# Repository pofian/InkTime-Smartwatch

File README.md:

# InkTime - Smartwatch

InkTime is an open-source, ultra-low-power smartwatch built around the Nordic nRF52840 SoC. It features a 1.54" E-Paper display, integrated battery management, and environmental/motion sensors, all optimized for extended battery life and BLE connectivity.

---

## Hardware Architecture

### Block Diagram

---

## Bill of Materials

| Reference Designators                                                                                                      | Quantity | Description                                                                                                               | Package                                    | Value                                                   | Manufacturer | Manufacturer Part Number | Vendor | Vendor Part Number | Top/Bottom |   |
|----------------------------------------------------------------------------------------------------------------------------|----------|---------------------------------------------------------------------------------------------------------------------------|--------------------------------------------|---------------------------------------------------------|--------------|--------------------------|--------|--------------------|------------|---|
|                                                                                                                            | 1        | PCB Board                                                                                                                 | Board                                      |                                                         |              |                          |        |                    |            |   |
| ANT1                                                                                                                       | 1        | Antennas 2.45GHz ANTENNA                                                                                                  | 2450AT18B100E_ANTC3216X140N                | 2450AT18B100E_2450AT18B100E                             |              |                          |        |                    | Top        |   |
| C1, C2, C17, C18                                                                                                           | 4        | Generic chip capacitor                                                                                                    | NORDIC_NRF_3_RESC0201_L                    | 12pF                                                    |              |                          |        |                    | Top        |   |
| C1-EP-DR, C24, C39                                                                                                         | 3        | CAPACITOR, European symbol                                                                                                | ESP32_WROVER_EAGLE-LTSPICE_C0402           | 10uF                                                    |              |                          |        |                    | Top        |   |
| C2-EP-DR                                                                                                                   | 1        | CAPACITOR, European symbol                                                                                                | ESP32_WROVER_EAGLE-LTSPICE_C0402           | 4.7uF/25V                                               |              |                          |        |                    | Top        |   |
| C3, C4                                                                                                                     | 2        | Generic chip capacitor                                                                                                    | NORDIC_NRF_3_RESC0201_L                    | 1pF                                                     |              |                          |        |                    | Top        |   |
| C5, C7, C8, C12, C19                                                                                                       | 5        | Generic chip capacitor                                                                                                    | NORDIC_NRF_3_RESC0201_L                    | 100nF                                                   |              |                          |        |                    | Top        |   |
| C6, C14, C20, C21                                                                                                          | 4        | Generic chip capacitor                                                                                                    | NORDIC_NRF_3_RESC0201_L                    | 4.7μF                                                   |              |                          |        |                    | Top        |   |
| C9                                                                                                                         | 1        | Generic chip capacitor                                                                                                    | NORDIC_NRF_3_RESC0201_L                    | 820pF                                                   |              |                          |        |                    | Top        |   |
| C10, C13, C22                                                                                                              | 3        | Generic chip capacitor                                                                                                    | NORDIC_NRF_3_RESC0201_L                    | N.C.                                                    |              |                          |        |                    | Top        |   |
| C11                                                                                                                        | 1        | Generic chip capacitor                                                                                                    | NORDIC_NRF_3_RESC0201_L                    | 100pF                                                   |              |                          |        |                    | Top        |   |
| C15                                                                                                                        | 1        | Generic chip capacitor                                                                                                    | NORDIC_NRF_3_RESC0201_L                    | 1.0μF                                                   |              |                          |        |                    | Top        |   |
| C16                                                                                                                        | 1        | Generic chip capacitor                                                                                                    | NORDIC_NRF_3_RESC0201_L                    | 47nF                                                    |              |                          |        |                    | Top        |   |
| C23                                                                                                                        | 1        | Check availability                                                                                                        | CAPC0201X13N                               | 0.1uF                                                   |              |                          |        |                    | Top        |   |
| C25, C33                                                                                                                   | 2        | CAPACITOR, European symbol                                                                                                | ESP32_WROVER_EAGLE-LTSPICE_C0402           | 22uF                                                    |              |                          |        |                    | Top        |   |
| C27, C34                                                                                                                   | 2        | Generic chip capacitor                                                                                                    | NORDIC_NRF_3_RESC0201_L                    | 0.1uF                                                   |              |                          |        |                    | Top        |   |
| C29, C30, C31, C43                                                                                                         | 4        | CAPACITOR, European symbol                                                                                                | ESP32_WROVER_EAGLE-LTSPICE_C0402           |                                                         |              |                          |        |                    | Top        |   |
| C32, C37, C38                                                                                                              | 3        | CAPACITOR, European symbol                                                                                                | ESP32_WROVER_EAGLE-LTSPICE_C0402           | 1uF                                                     |              |                          |        |                    | Top        |   |
| C42                                                                                                                        | 1        | Generic chip capacitor                                                                                                    | NORDIC_NRF_3_RESC0201_L                    |                                                         |              |                          |        |                    | Top        |   |
| D2, D4, D5                                                                                                                 | 3        | ON SEMICONDUCTOR - MBR0530 - DIODE, SCHOTTKY, 0.5A, 30V, SOD-123                                                          | SOD3716X135N                               | ESP32_C6_LIBRARY_5_MBR0530                              |              |                          |        |                    | Top        |   |
| D3                                                                                                                         | 1        | Low Cap. ESD Protection Auto SOT-23-6 STMicroelectronics USBLC6-2SC6Y, Dual Uni-Directional TVS Diode Array, 6-Pin SOT-23 | SOT95P280X145-6N                           | ESP32_C6_LIBRARY_3_USBLC6-2SC6Y                         |              |                          |        |                    | Top        |   |
| EPD_C1, EPD_C2, EPD_C6, EPD_C7, EPD_C8, EPD_C9, EPD_C10, EPD_C11, EPD_C12                                                  | 9        | CAPACITOR, European symbol                                                                                                | ESP32_WROVER_EAGLE-LTSPICE_C0402           | 1uF/50V                                                 |              |                          |        |                    | Top        |   |
| EPD_C5                                                                                                                     | 1        | CAPACITOR, European symbol                                                                                                | ESP32_WROVER_EAGLE-LTSPICE_C0402           | 0.1uF/50V                                               |              |                          |        |                    | Top        |   |
| IC1                                                                                                                        | 1        | Charger IC Lithium Ion/Polymer, Lithium Iron Phosphate 8-DSBGA (1.6x1.1)                                                  | BQ25180YBGR_BGA8C40P2X4_100X155X50         | BQ25180YBGR_BQ25180YBGR                                 |              |                          |        |                    | Top        |   |
| IC2                                                                                                                        | 1        | Haptic Driver for ERM/LRA with Built-In Library and Smart Loop Architecture                                               | DRV2605YZFR_BGA9C50P3X3_144X144X62         | DRV2605YZFR_DRV2605YZFR                                 |              |                          |        |                    | Top        |   |
| IC3                                                                                                                        | 1        | Accelerometers Triaxial low-g 12bit Acceleration Sensor                                                                   | BMA423_BMA423                              | BMA423_BMA423                                           |              |                          |        |                    | Top        |   |
| IC9                                                                                                                        | 1        | Buck-Boost Regulator Positive Output Step-Up/Step-Down I2C DC-DC Controller IC 15-WL-CSP (BSC) (1.4x2.3)                  | RT6160AWSC_BGA15C40P3X5_140X230X60         | RT6160AWSC_RT6160AWSC                                   |              |                          |        |                    | Top        |   |
| J1                                                                                                                         | 1        | FFC & FPC Connectors 0.5mm FPC RA SMT Dual Contact 24Ckt                                                                  | 503480-2400_5034802400                     | 503480-2400_503480-2400                                 |              |                          |        |                    | Top        |   |
| J2                                                                                                                         | 1        | CABLE ADAPTER 6 POS                                                                                                       | TC2030-IDC_TC2030IDC                       | TC2030-IDC_TC2030-IDC                                   |              |                          |        |                    | Top        |   |
| J4                                                                                                                         | 1        | Check availability                                                                                                        | KINGHELM_KH-TYPE-C-16P                     | KH-TYPE-C-16P_KH-TYPE-C-16P                             |              |                          |        |                    | Top        |   |
| L1, L7                                                                                                                     | 2        | Generic chip inductor                                                                                                     | NORDIC_NRF_2_RESC0402_L                    |                                                         |              |                          |        |                    | Top        |   |
| L2                                                                                                                         | 1        | Generic chip inductor                                                                                                     | NORDIC_NRF_2_RESC0402_L                    | 10uH                                                    |              |                          |        |                    | Top        |   |
| L3                                                                                                                         | 1        | Generic chip inductor                                                                                                     | NORDIC_NRF_2_RESC0402_L                    | 15nH                                                    |              |                          |        |                    | Top        |   |
| L5                                                                                                                         | 1        | Generic chip inductor                                                                                                     | NORDIC_NRF_2_RESC0402_L                    | 68uH                                                    |              |                          |        |                    | Top        |   |
| Q1                                                                                                                         | 1        | P-channel MOSFETs                                                                                                         | ESP32_WROVER_SPARKFUN-DISCRETESEMI_SOT23-3 | 20V/4.2A/52mΩ/1.4W                                      |              |                          |        |                    | Top        |   |
| Q3                                                                                                                         | 1        | MOSFET N-Ch 30V 1.5A TrenchFET SC70 Vishay Si1308EDL-T1-GE3 N-channel MOSFET Transistor, 1.5 A, 30 V, 3-Pin SC-70         | SOT65P210X110-3N                           | ESP32_C6_LIBRARY_6_SI1308EDL-T1-GE3                     |              |                          |        |                    | Top        |   |
| R_PWR_EPD, R2_EP_DR, R5, R7, R8, R9                                                                                        | 6        | 7.68k 0201 Thin Film Surface Mount Fixed Resistor +/-0.5% 0.031W CPF0201D7K68C1                                           | CPF0201D7K68C1_0201                        | 10K                                                     |              |                          |        |                    | Top        |   |
| R_TYPE_SEL                                                                                                                 | 1        | 7.68k 0201 Thin Film Surface Mount Fixed Resistor +/-0.5% 0.031W CPF0201D7K68C1                                           | CPF0201D7K68C1_0201                        | 2.2                                                     |              |                          |        |                    | Top        |   |
| R1_EP_DR                                                                                                                   | 1        | 7.68k 0201 Thin Film Surface Mount Fixed Resistor +/-0.5% 0.031W CPF0201D7K68C1                                           | CPF0201D7K68C1_0201                        | 0.47                                                    |              |                          |        |                    | Top        |   |
| R1_USB, R2_USB                                                                                                             | 2        | 7.68k 0201 Thin Film Surface Mount Fixed Resistor +/-0.5% 0.031W CPF0201D7K68C1                                           | CPF0201D7K68C1_0201                        | 5K1                                                     |              |                          |        |                    | Top        |   |
| R2, R4                                                                                                                     | 2        | 7.68k 0201 Thin Film Surface Mount Fixed Resistor +/-0.5% 0.031W CPF0201D7K68C1                                           | CPF0201D7K68C1_0201                        | 0                                                       |              |                          |        |                    | Top        |   |
| R3                                                                                                                         | 1        | 7.68k 0201 Thin Film Surface Mount Fixed Resistor +/-0.5% 0.031W CPF0201D7K68C1                                           | R0201                                      | 0                                                       |              |                          |        |                    | Top        |   |
| R17, R18                                                                                                                   | 2        | 7.68k 0201 Thin Film Surface Mount Fixed Resistor +/-0.5% 0.031W CPF0201D7K68C1                                           | CPF0201D7K68C1_0201                        | 3K3                                                     |              |                          |        |                    | Top        |   |
| SJ1                                                                                                                        | 1        | SMD solder JUMPER                                                                                                         | JUMPER_SJ                                  |                                                         |              |                          |        |                    | Top        |   |
| SW_DN, SW_ENT, SW_UP                                                                                                       | 3        |                                                                                                                           | SW_EVP-AKE31A_PAN                          | 2025-10-22_07-23-44_LIBRARY_EVP-AKE31ASW_EVP-AKE31A_PAN |              |                          |        |                    | Top        |   |
| TP_3.3V, TP_3V3, TP_BAT_GND, TP_GND, TP_ON, TP_OP, TP_RESET, TP_SCL, TP_SDA, TP_SWDCLK, TP_SWDIO, TP_SWO, TP_VBAT, TP_VREG | 14       | Test pad                                                                                                                  | HECTOR_WATCH_1_TP20R                       | HECTOR_WATCH_1_TPTP20R                                  |              |                          |        |                    | Top        |   |
| U1                                                                                                                         | 1        | nRF52840                                                                                                                  | NORDIC_NRF_4_AQFN50P700X700X85_HS-74N      | NORDIC_NRF_4_NRF52840_QF                                |              |                          |        |                    | Top        |   |
| U3                                                                                                                         | 1        | Check availability                                                                                                        | SON50P200X200X80-9N                        | ESP32_C6_LIBRARY_MAX17048G+T10                          |              |                          |        |                    | Top        |   |
| X1                                                                                                                         | 1        |                                                                                                                           | NORDIC_NRF_BT-XTAL_2016_N                  | 32MHz                                                   |              |                          |        |                    | Top        |   |
| X2                                                                                                                         | 1        |                                                                                                                           | NORDIC_NRF_1_XTAL_3215_N                   |                                                         |              |                          |        |                    | Top        |   |

---

## Hardware Functionality

### 1. Power Architecture
The system is powered by a 250mAh LiPo battery.

* **Charging:** The BQ25180 manages 5V input from USB-C. It features I2C configurable charge currents and safety timers.
* **Regulation:** A high-efficiency RT6160 buck-boost converter provides a stable 3.3V rail. This maintains 3.3V even when the battery drops to 3.0V.
* **Monitoring:** The MAX17048 uses the ModelGauge algorithm to provide precise SOC (State of Charge) data.

### 2. Display System
A 1.54" E-Paper display (200x200) is used for zero power consumption when static.

* **Interface:** 4-wire SPI + DC/RST/BUSY control lines.
* **Booster Circuit:** An external inductor-based boost circuit generates the ±15V gates voltages required for the e-ink capsules.

### 3. Sensors and Feedback
* **IMU:** The BMA423 provides step counting and tilt-to-wake functionality via I2C interrupts.
* **Haptics:** The DRV2605 drives a 10mm coin vibration motor, providing tactile effects.

---

## Design Log & Decisions

### DRC Exceptions
The following errors were reviewed and manually accepted in the final design:

* **Pad-to-Trace Clearance:** Errors caused by traces passing between MCU pads; these are unavoidable due to the high-density pinout and the limited routing escape paths of the nRF52840 package.
* **Via Proximity:** Errors caused by vias placed in close proximity to each other, necessitated by the same spatial constraints in the micro-pitch area of the SoC.

### Layout Decisions
* **Stack-up:** 4-layer PCB to ensure a solid GND plane (Layer 2) for RF performance.
* **Power Traces:** All power rails (VBUS, VBAT, 3V3, etc.) use a 0.3mm width for current spikes.
* **Signal Integrity:** Data signals use 0.15mm width. No 90-degree angles were used; all corners are 45 degrees.

### Mechanical Placement
* **USB-C Port:** Centered on the top edge, slightly protruding from the PCB boundary for seamless enclosure alignment.
* **User Input:** Three tactile buttons are located on the bottom edge.

### Polygon & Outline Management
* **GND Polygon Overlaps:** Same-net (GND) clearance warnings between overlapping polygons on different layers were ignored as they pose no electrical risk.

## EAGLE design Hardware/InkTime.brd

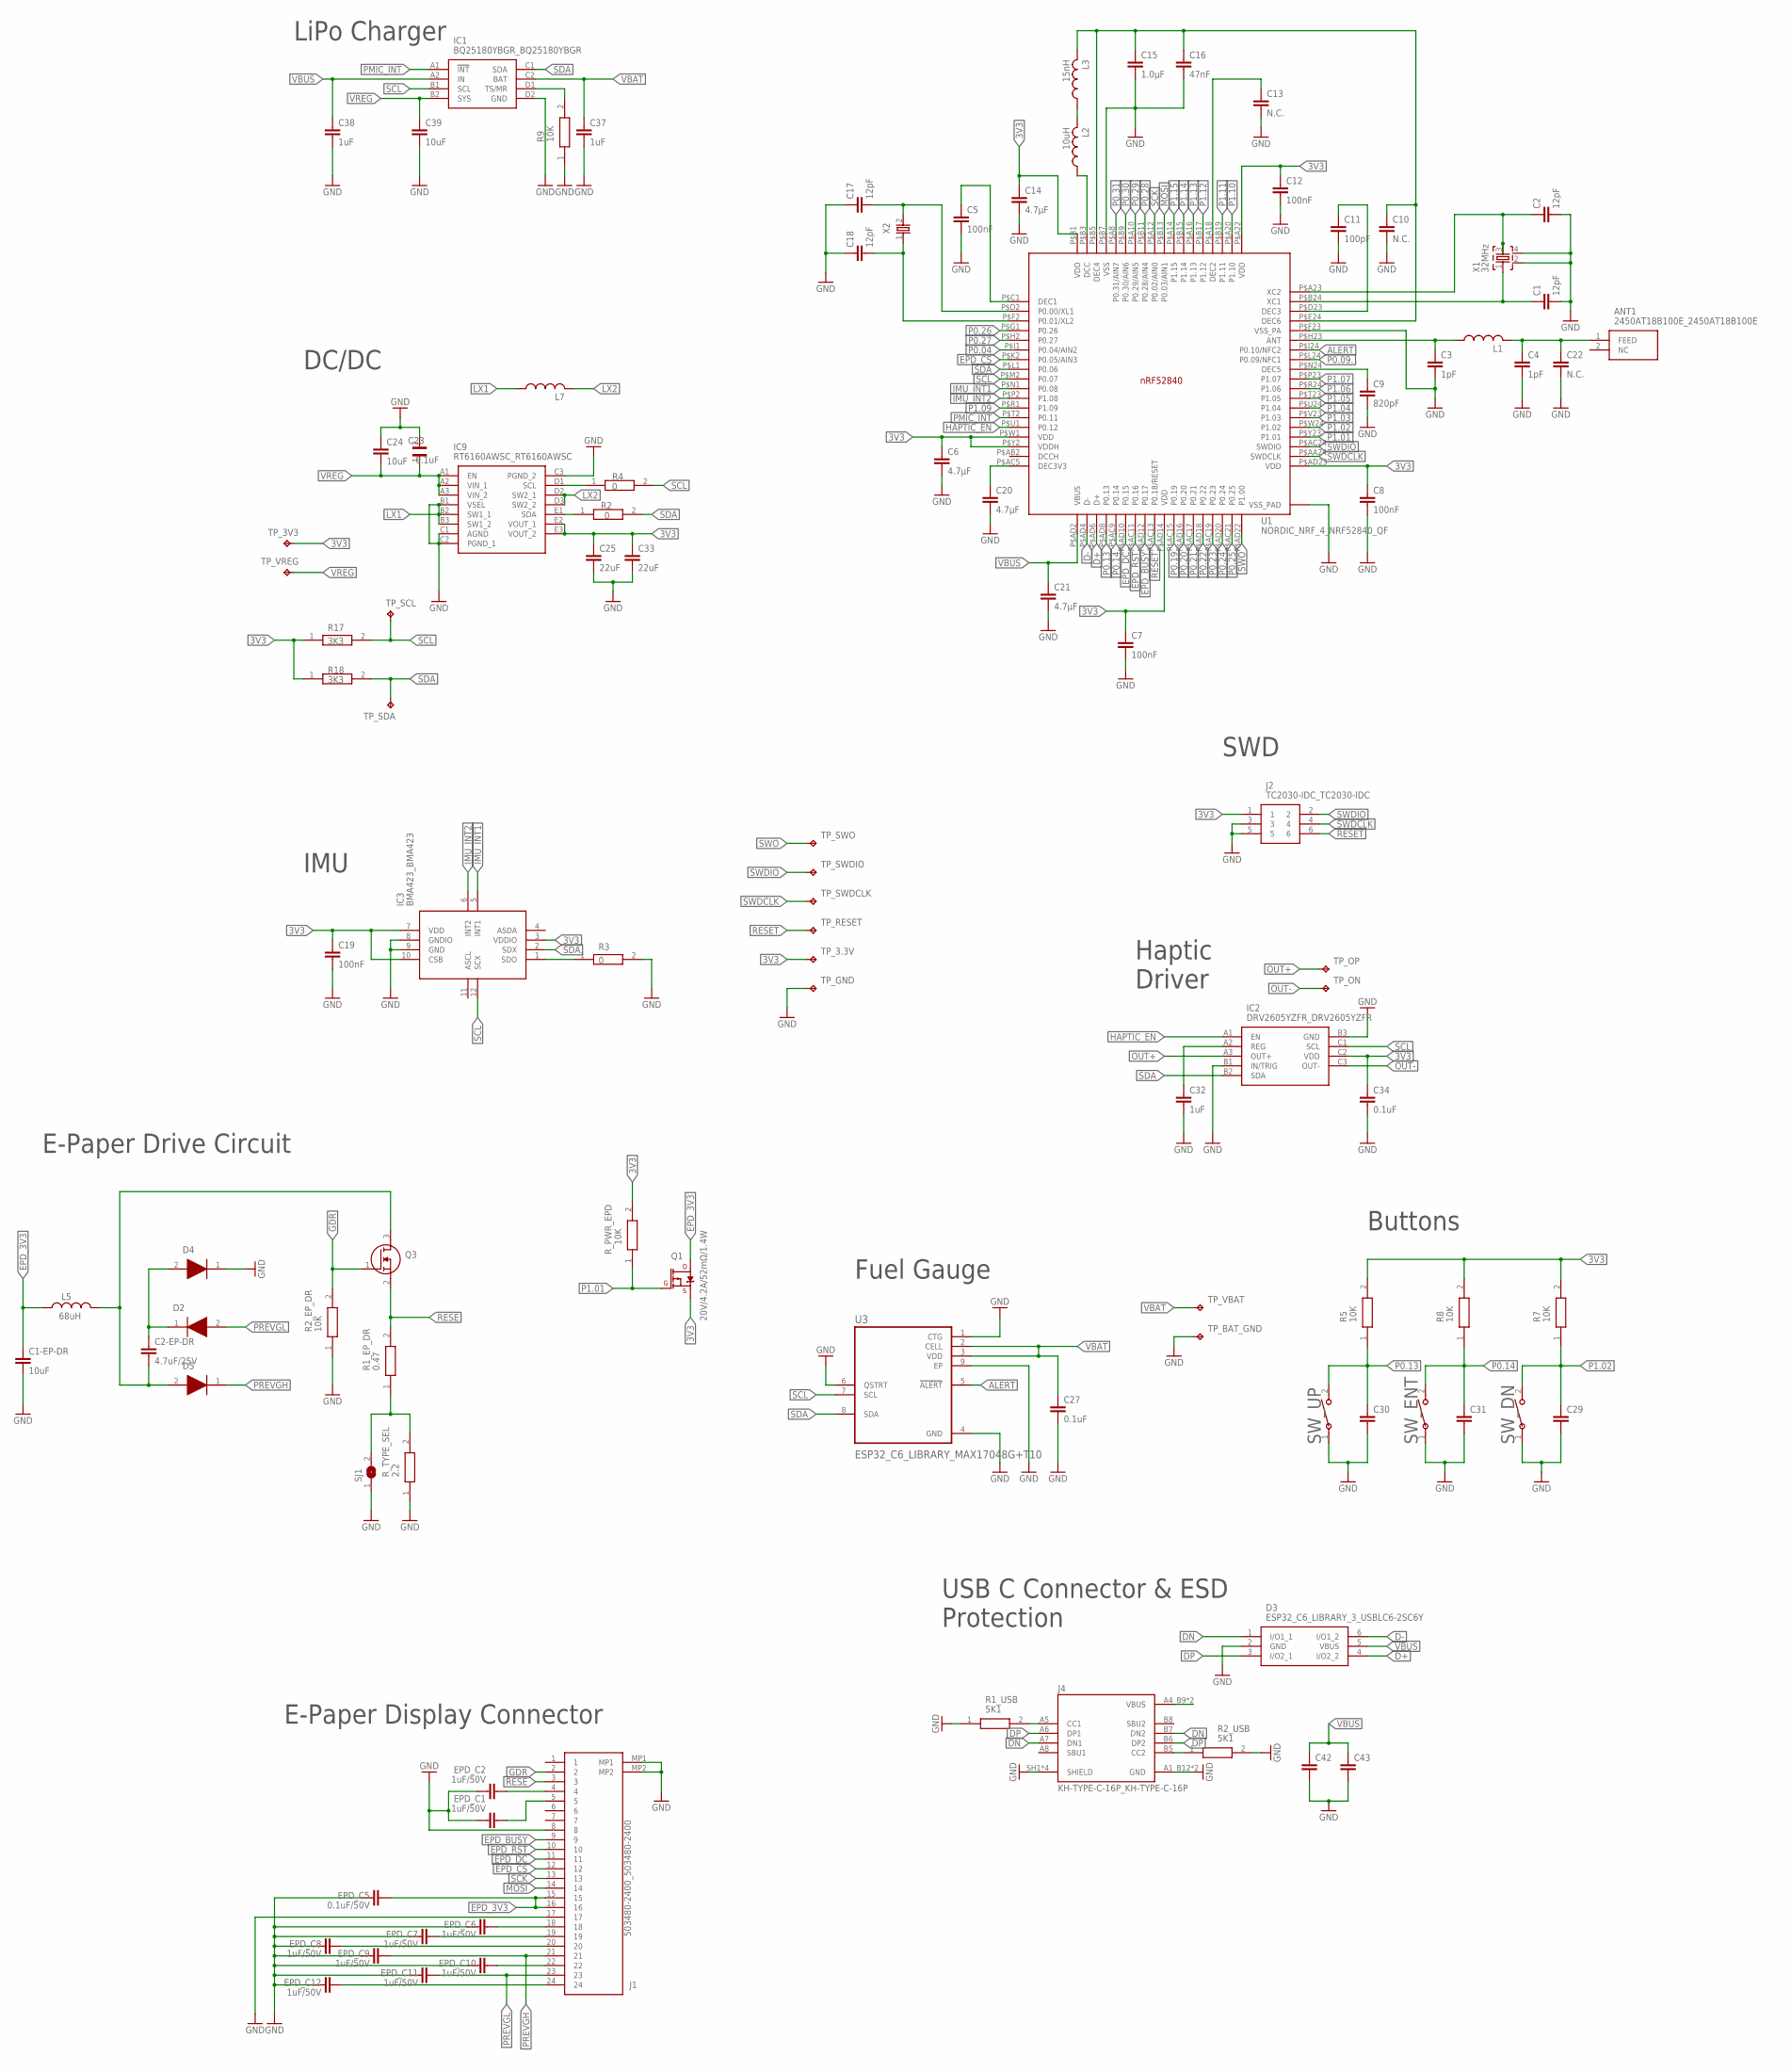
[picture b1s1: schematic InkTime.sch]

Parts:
ANT1: 2450AT18B100E_2450AT18B100E; 2450AT18B100E_ANTC3216X140N
C1, C2, C17, C18: 12pF; NORDIC_NRF_3_RESC0201_L
C1-EP-DR, C24, C39: 10uF; ESP32_C6_LIBRARY_1_ESP32_WROVER_EAGLE-LTSPICE_C0402
C2-EP-DR: 4.7uF/25V; ESP32_C6_LIBRARY_1_ESP32_WROVER_EAGLE-LTSPICE_C0402
C3, C4: 1pF; NORDIC_NRF_3_RESC0201_L
C5, C7, C8, C12, C19: 100nF; NORDIC_NRF_3_RESC0201_L
C6, C14, C20, C21: 4.7μF; NORDIC_NRF_3_RESC0201_L
C9: 820pF; NORDIC_NRF_3_RESC0201_L
C10, C13, C22: N.C.; NORDIC_NRF_3_RESC0201_L
C11: 100pF; NORDIC_NRF_3_RESC0201_L
C15: 1.0μF; NORDIC_NRF_3_RESC0201_L
C16: 47nF; NORDIC_NRF_3_RESC0201_L
C23: 0.1uF; GRM011R60J152KE01L_2_CAPC0201X13N
C25, C33: 22uF; ESP32_C6_LIBRARY_1_ESP32_WROVER_EAGLE-LTSPICE_C0402
C27, C34: 0.1uF; NORDIC_NRF_3_RESC0201_L
C29, C30, C31, C43: ESP32_C6_LIBRARY_1_ESP32_WROVER_EAGLE-LTSPICE_CC0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; ESP32_C6_LIBRARY_1_ESP32_WROVER_EAGLE-LTSPICE_C0402
C32, C37, C38: 1uF; ESP32_C6_LIBRARY_1_ESP32_WROVER_EAGLE-LTSPICE_C0402
C42: NORDIC_NRF_3_CAPACITOR_0201_L; NORDIC_NRF_3_RESC0201_L
D2, D4, D5: ESP32_C6_LIBRARY_5_MBR0530; ESP32_C6_LIBRARY_5_SOD3716X135N
D3: ESP32_C6_LIBRARY_3_USBLC6-2SC6Y; ESP32_C6_LIBRARY_3_SOT95P280X145-6N
EPD_C1, EPD_C2, EPD_C6, EPD_C7, EPD_C8, EPD_C9, EPD_C10, EPD_C11, EPD_C12: 1uF/50V; ESP32_C6_LIBRARY_1_ESP32_WROVER_EAGLE-LTSPICE_C0402
EPD_C5: 0.1uF/50V; ESP32_C6_LIBRARY_1_ESP32_WROVER_EAGLE-LTSPICE_C0402
IC1: BQ25180YBGR_BQ25180YBGR; BQ25180YBGR_BGA8C40P2X4_100X155X50
IC2: DRV2605YZFR_DRV2605YZFR; DRV2605YZFR_BGA9C50P3X3_144X144X62
IC3: BMA423_BMA423
IC9: RT6160AWSC_RT6160AWSC; RT6160AWSC_BGA15C40P3X5_140X230X60
J1: 503480-2400_503480-2400; 503480-2400_5034802400
J2: TC2030-IDC_TC2030-IDC; TC2030-IDC_TC2030IDC
J4: KH-TYPE-C-16P_KH-TYPE-C-16P; KH-TYPE-C-16P_KINGHELM_KH-TYPE-C-16P
L1, L7: NORDIC_NRF_2_INDUCTOR_0402_L; NORDIC_NRF_2_RESC0402_L
L2: 10uH; NORDIC_NRF_2_RESC0402_L
L3: 15nH; NORDIC_NRF_2_RESC0402_L
L5: 68uH; NORDIC_NRF_2_RESC0402_L
Q1: 20V/4.2A/52mΩ/1.4W; ESP32_C6_LIBRARY_4_ESP32_C6_LIBRARY_4_ESP32_C6_LIBRARY_4_ES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
Q3: ESP32_C6_LIBRARY_6_SI1308EDL-T1-GE3; ESP32_C6_LIBRARY_6_SOT65P210X110-3N
R1_EP_DR: 0.47; CPF0201D7K68C1_0201
R1_USB, R2_USB: 5K1; CPF0201D7K68C1_0201
R2, R4: 0; CPF0201D7K68C1_0201
R2_EP_DR, R5, R7, R8, R9: 10K; CPF0201D7K68C1_0201
R3: 0; ERA-1AEB3401C_0201
R17, R18: 3K3; CPF0201D7K68C1_0201
R_PWR_EPD: 10K; CPF0201D7K68C1_0201
R_TYPE_SEL: 2.2; CPF0201D7K68C1_0201
SJ1: ESP32_C6_LIBRARY_7_JUMPER_SJ
SW_DN: 2025-10-22_07-23-44_LIBRARY_EVP-AKE31ASW_EVP-AKE3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; 2025-10-22_07-23-44_LIBRARY_SW_EVP-AKE31A_PAN
SW_ENT: 2025-10-22_07-23-44_LIBRARY_EVP-AKE31ASW_EVP-AKE3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; 2025-10-22_07-23-44_LIBRARY_SW_EVP-AKE31A_PAN
SW_UP: 2025-10-22_07-23-44_LIBRARY_EVP-AKE31ASW_EVP-AKE3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; 2025-10-22_07-23-44_LIBRARY_SW_EVP-AKE31A_PAN
TP_3.3V, TP_3V3: HECTOR_WATCH_1_TPTP20R; HECTOR_WATCH_1_TP20R
TP_BAT_GND: HECTOR_WATCH_1_TPTP20R; HECTOR_WATCH_1_TP20R
TP_GND: HECTOR_WATCH_1_TPTP20R; HECTOR_WATCH_1_TP20R
TP_ON: HECTOR_WATCH_1_TPTP20R; HECTOR_WATCH_1_TP20R
TP_OP: HECTOR_WATCH_1_TPTP20R; HECTOR_WATCH_1_TP20R
TP_RESET: HECTOR_WATCH_1_TPTP20R; HECTOR_WATCH_1_TP20R
TP_SCL: HECTOR_WATCH_1_TPTP20R; HECTOR_WATCH_1_TP20R
TP_SDA: HECTOR_WATCH_1_TPTP20R; HECTOR_WATCH_1_TP20R
TP_SWDCLK: HECTOR_WATCH_1_TPTP20R; HECTOR_WATCH_1_TP20R
TP_SWDIO: HECTOR_WATCH_1_TPTP20R; HECTOR_WATCH_1_TP20R
TP_SWO: HECTOR_WATCH_1_TPTP20R; HECTOR_WATCH_1_TP20R
TP_VBAT: HECTOR_WATCH_1_TPTP20R; HECTOR_WATCH_1_TP20R
TP_VREG: HECTOR_WATCH_1_TPTP20R; HECTOR_WATCH_1_TP20R
U1: NORDIC_NRF_4_NRF52840_QF; NORDIC_NRF_4_AQFN50P700X700X85_HS-74N
U3: ESP32_C6_LIBRARY_MAX17048G+T10; ESP32_C6_LIBRARY_SON50P200X200X80-9N
X1: 32MHz; NORDIC_NRF_BT-XTAL_2016_N
X2: NORDIC_NRF_1_XTAL_32KHZ; NORDIC_NRF_1_XTAL_3215_N

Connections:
3V3: C6.1, C7.1, C8.1, C12.1, C14.1, C19.1, C25.1, C33.1, C34.1, IC2.C2 (VDD), IC3.3 (VDDIO), IC3.7 (VDD), IC3.10 (CSB), IC9.E2 (VOUT_1), IC9.E3 (VOUT_2), J2.1, Q1.2 (S), R5.2, R7.2, R8.2, R17.1, R18.1, R_PWR_EPD.2, TP_3.3V.TP, TP_3V3.TP, U1.P$A22 (VDD), U1.P$AD14 (VDD), U1.P$AD23 (VDD), U1.P$B1 (VDD), U1.P$W1 (VDD), U1.P$Y2 (VDDH)
ALERT: U1.P$J24 (P0.10/NFC2), U3.5 (!ALERT)
D+: D3.4 (I/O2_2), U1.P$AD6 (D+)
D-: D3.6 (I/O1_2), U1.P$AD4 (D-)
DN: D3.1 (I/O1_1), J4.A7 (DN1), J4.B7 (DN2)
DP: D3.3 (I/O2_1), J4.A6 (DP1), J4.B6 (DP2)
EPD_3V3: C1-EP-DR.1, EPD_C5.2, J1.15, J1.16, L5.1, Q1.3 (D)
EPD_BUSY: J1.9, U1.P$AD12 (P0.17)
EPD_CS: J1.12, U1.P$K2 (P0.05/AIN3)
EPD_DC: J1.11, U1.P$AD10 (P0.15)
EPD_RST: J1.10, U1.P$AC11 (P0.16)
GDR: J1.1, J1.2, J1.MP1, J1.MP2, Q3.1 (G), R2_EP_DR.2
GND: C1.2, C1-EP-DR.2, C2.2, C3.2, C4.2, C5.2, C6.2, C7.2, C8.2, C9.2, C10.2, C11.2, C12.2, C13.2, C14.2, C15.2, C16.2, C17.1, C18.1, C19.2, C20.2, C21.2, C22.2, C23.2, C24.1, C25.2, C27.2, C29.2, C30.2, C31.2, C32.2, C33.2, C34.2, C37.2, C38.2, C39.2, C42.2, C43.2, D3.2 (GND), D4.1 (K), EPD_C1.1, EPD_C2.1, IC1.D2 (GND), IC2.B1 (IN/TRIG), IC2.B3 (GND), IC3.8 (GNDIO), IC3.9 (GND), IC9.C3 (PGND_2), J1.8, J1.17, J2.3, J2.5, J4.A1_B12 (GND), J4.A12_B1 (GND), J4.SH1 (SHIELD), J4.SH2 (SHIELD), J4.SH3 (SHIELD), J4.SH4 (SHIELD), R1_USB.1, R2_EP_DR.1, R2_USB.2, R3.2, R9.1, R_TYPE_SEL.1, SJ1.1, SW_DN.1, SW_ENT.1, SW_UP.1, TP_BAT_GND.TP, TP_GND.TP, U1.P$74 (VSS_PAD), U1.P$75 (VSS_PAD), U1.P$76 (VSS_PAD), U1.P$77 (VSS_PAD), U1.P$78 (VSS_PAD), U1.P$79 (VSS_PAD), U1.P$80 (VSS_PAD), U1.P$81 (VSS_PAD), U1.P$82 (VSS_PAD), U1.P$83 (VSS_PAD), U1.P$84 (VSS_PAD), U1.P$85 (VSS_PAD), U1.P$86 (VSS_PAD), U1.P$87 (VSS_PAD), U1.P$88 (VSS_PAD), U1.P$89 (VSS_PAD), U1.P$90 (VSS_PAD), U1.P$B7 (VSS), U1.P$F23 (VSS_PA), U3.1 (CTG), U3.4 (GND), U3.6 (QSTRT), U3.9 (EP), X1.2, X1.4
HAPTIC_EN: IC2.A1 (EN), U1.P$U1 (P0.12)
IMU_INT1: IC3.5 (INT1), U1.P$N1 (P0.08)
IMU_INT2: IC3.6 (INT2), U1.P$P2 (P1.08)
LX1: IC9.B1 (VSEL), IC9.B2 (SW1_1), IC9.B3 (SW1_2), IC9.C1 (AGND), IC9.C2 (PGND_1), L7.1
LX2: IC9.D2 (SW2_1), IC9.D3 (SW2_2), L7.2
MOSI: J1.14, U1.P$B13 (P0.03/AIN1)
unnamed: L2.1, U1.P$B3 (DCC)
unnamed: C5.1, U1.P$C1 (DEC1)
unnamed: L2.2, L3.1
unnamed: C10.1, C15.1, C16.1, L3.2, U1.P$B5 (DEC4), U1.P$E24 (DEC6)
unnamed: C2-EP-DR.1, D2.1 (K), D4.2 (A)
unnamed: C13.1, U1.P$A18 (DEC2)
unnamed: IC9.D1 (SCL), R4.1
unnamed: C11.1, U1.P$D23 (DEC3)
unnamed: C32.1, IC2.A2 (REG)
unnamed: IC9.E1 (SDA), R2.1
unnamed: IC1.D1 (TS/MR), R9.2
unnamed: EPD_C6.2, J1.18
unnamed: EPD_C7.2, J1.19
unnamed: EPD_C8.2, J1.20
unnamed: IC3.1 (SDO), R3.1
unnamed: C2-EP-DR.2, D5.2 (A), L5.2, Q3.3 (D)
unnamed: J4.A5 (CC1), R1_USB.2
unnamed: J4.A4_B9 (VBUS), J4.A9_B4 (VBUS)
unnamed: C17.2, U1.P$D2 (P0.00/XL1), X2.2
unnamed: C18.2, U1.P$F2 (P0.01/XL2), X2.1
unnamed: EPD_C10.2, J1.22
unnamed: C20.1, U1.P$AC5 (DEC3V3)
unnamed: C2.1, U1.P$A23 (XC2), X1.3
unnamed: J4.B5 (CC2), R2_USB.1
unnamed: EPD_C12.2, J1.24
unnamed: C1.1, U1.P$B24 (XC1), X1.1
unnamed: ANT1.1 (FEED), C4.1, C22.1, L1.2
unnamed: C9.1, U1.P$N24 (DEC5)
unnamed: C3.1, L1.1, U1.P$H23 (ANT)
unnamed: EPD_C1.2, J1.5
unnamed: EPD_C2.2, J1.4
unnamed: R1_EP_DR.1, R_TYPE_SEL.2, SJ1.2
OUT+: IC2.A3 (OUT+), TP_OP.TP
OUT-: IC2.C3 (OUT-), TP_ON.TP
P0.04: U1.P$J1 (P0.04/AIN2)
P0.09.: U1.P$L24 (P0.09/NFC1)
P0.13: C30.1, R5.1, SW_UP.2, U1.P$AD8 (P0.13)
P0.14: C31.1, R8.1, SW_ENT.2, U1.P$AC9 (P0.14)
P0.19: U1.P$AC15 (P0.19)
P0.20: U1.P$AD16 (P0.20)
P0.21: U1.P$AC17 (P0.21)
P0.22: U1.P$AD18 (P0.22)
P0.23: U1.P$AC19 (P0.23)
P0.24: U1.P$AD20 (P0.24)
P0.25: U1.P$AC21 (P0.25)
P0.26: U1.P$G1 (P0.26)
P0.27: U1.P$H2 (P0.27)
P0.28: U1.P$B11 (P0.28/AIN4)
P0.29: U1.P$A10 (P0.29/AIN5)
P0.30: U1.P$B9 (P0.30/AIN6)
P0.31: U1.P$A8 (P0.31/AIN7)
P1.01: Q1.1 (G), R_PWR_EPD.1, U1.P$Y23 (P1.01)
P1.02: C29.1, R7.1, SW_DN.2, U1.P$W24 (P1.02)
P1.03: U1.P$V23 (P1.03)
P1.04: U1.P$U24 (P1.04)
P1.05: U1.P$T23 (P1.05)
P1.06: U1.P$R24 (P1.06)
P1.07: U1.P$P23 (P1.07)
P1.09: U1.P$R1 (P1.09)
P1.10: U1.P$A20 (P1.10)
P1.11: U1.P$B19 (P1.11)
P1.12: U1.P$B17 (P1.12)
P1.13: U1.P$A16 (P1.13)
P1.14: U1.P$B15 (P1.14)
P1.15: U1.P$A14 (P1.15)
PMIC_INT: IC1.A1 (!INT), U1.P$T2 (P0.11)
PREVGH: D5.1 (K), EPD_C9.2, J1.21
PREVGL: D2.2 (A), EPD_C5.1, EPD_C6.1, EPD_C7.1, EPD_C8.1, EPD_C9.1, EPD_C10.1, EPD_C11.1, EPD_C11.2, EPD_C12.1, J1.23
RESE: J1.3, Q3.2 (S), R1_EP_DR.2
RESET: J2.6, TP_RESET.TP, U1.P$AC13 (P0.18/RESET)
SCK: J1.13, U1.P$A12 (P0.02/AIN0)
SCL: IC1.B1 (SCL), IC2.C1 (SCL), IC3.12 (SCX), R4.2, R17.2, TP_SCL.TP, U1.P$M2 (P0.07), U3.7 (SCL)
SDA: IC1.C1 (SDA), IC2.B2 (SDA), IC3.2 (SDX), R2.2, R18.2, TP_SDA.TP, U1.P$L1 (P0.06), U3.8 (SDA)
SWDCLK: J2.4, TP_SWDCLK.TP, U1.P$AA24 (SWDCLK)
SWDIO: J2.2, TP_SWDIO.TP, U1.P$AC24 (SWDIO)
SWO: TP_SWO.TP, U1.P$AD22 (P1.00)
VBAT: C27.1, C37.1, IC1.C2 (BAT), TP_VBAT.TP, U3.2 (CELL), U3.3 (VDD)
VBUS: C21.1, C38.1, C42.1, C43.1, D3.5 (VBUS), IC1.A2 (IN), U1.P$AD2 (VBUS)
VREG: C23.1, C24.2, C39.1, IC1.B2 (SYS), IC9.A1 (EN), IC9.A2 (VIN_1), IC9.A3 (VIN_2), TP_VREG.TP

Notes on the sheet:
LiPo Charger
DC/DC
IMU
SWD
Haptic Driver
Buttons
Fuel Gauge
E-Paper Drive Circuit
E-Paper Display Connector
USB C Connector & ESD Protection

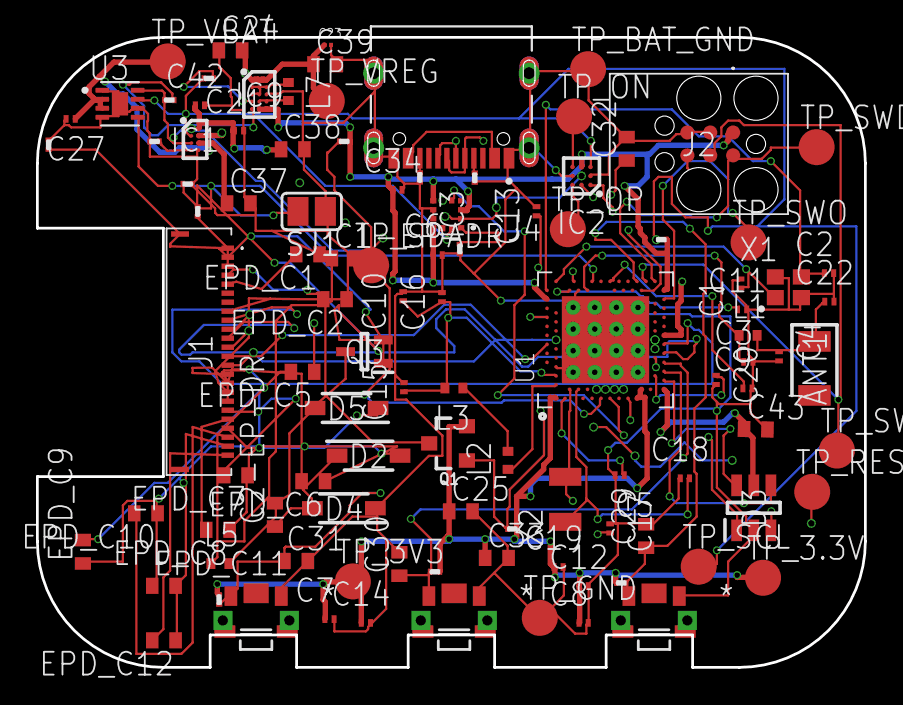
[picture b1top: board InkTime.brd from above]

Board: 4 copper layers, 46.0 x 35.0 mm, 105 parts (0 on the bottom side), 71 nets.

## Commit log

2026-04-10 Finish Schematic & Add PCB
2026-04-16 Finish PCB & Add 3D Design
2026-04-16 Add block diagram & Modify README
2026-04-16 Modify README

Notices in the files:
parts and their libraries:
COPYRIGHT: Copyright (C) 2025 Ultra Librarian. All rights reserved.
